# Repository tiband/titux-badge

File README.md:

# TiTux badge

## board

The board is designed in KiCad and uses a dual sided pcb while only using one side for the components. It features an ATtiny84 with 6 LEDs and a switch powered by a 3 V button cell. The example above was manufactured by [OSH Park].

## code

The challenge is to come up with your own interesting light shows, games, etc. for the badge. This repo includes a basic Arduino sketch using the [ATTinyCore] to get you started.

Use some crocodile clips and an AVR ISP programmer like a standard Arduino UNO with the [ISP sketch] and a 10 μF capacitor.

## licence

The design and example firmware are licenced under `GPL-3.0-or-later`.

[OSH Park]: https://oshpark.com/
[ATTinyCore]: https://github.com/SpenceKonde/ATTinyCore
[ISP sketch]: https://www.arduino.cc/en/tutorial/arduinoISP

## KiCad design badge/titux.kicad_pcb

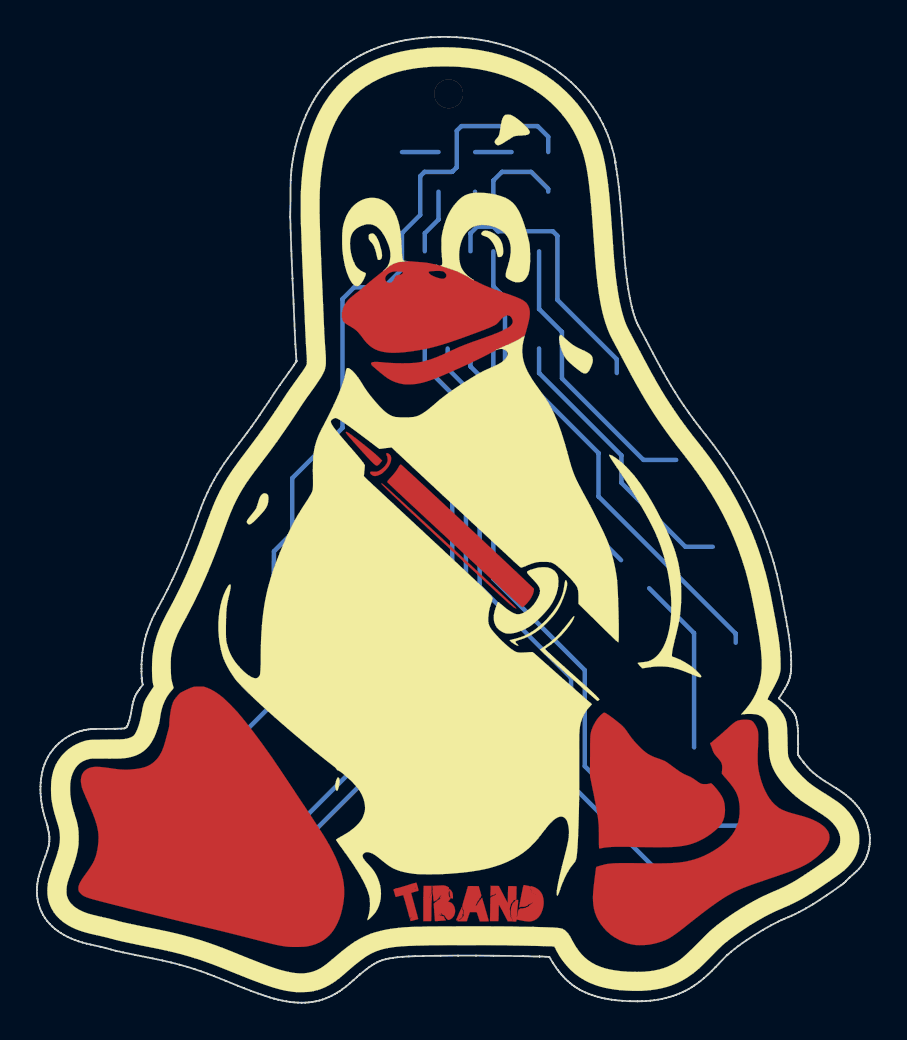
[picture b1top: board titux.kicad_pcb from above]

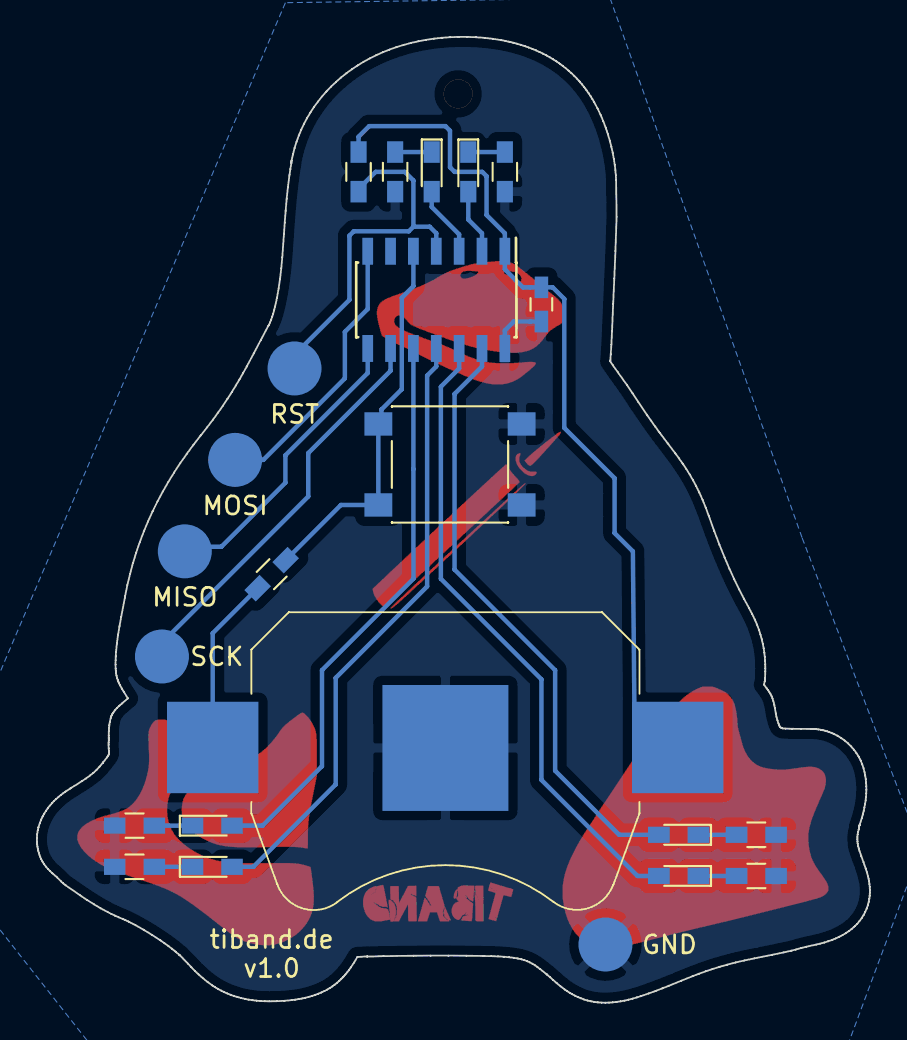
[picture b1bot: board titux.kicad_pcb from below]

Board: 2 copper layers, 46.3 x 53.7 mm, 23 parts (23 on the bottom side), 19 nets.

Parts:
BT1: Battery_Cell; KZH_20SMD_1x20mm-CoinCell
C1: 100n; C_0603_HandSoldering
D1, D2, D3, D4, D5, D6: LED_Small; LED_0603_HandSoldering
GND: Conn_01x01; KrokoPad
MISO: Conn_01x01; KrokoPad
MOSI: Conn_01x01; KrokoPad
R1, R2, R3, R4, R5, R6: R_Small; R_0603_HandSoldering
R10, R11: 10k; R_0603_HandSoldering
RST: Conn_01x01; KrokoPad
SCK: Conn_01x01; KrokoPad
SW1: SW_Push; Switch_SMD_rotated_6x6x4,3
U1: ATtiny84A-SSU; SOIC-14_3.9x8.7mm_Pitch1.27mm

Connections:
/LED_B1: D1.2, U1.12
/LED_B2: D3.2, U1.10
/LED_B3: D5.2, U1.3
/LED_R1: D2.2, U1.13
/LED_R2: D4.2, U1.11
/LED_R3: D6.2, U1.2
/MISO: MISO.1, U1.8
/MOSI: MOSI.1, U1.7
/RESET: R11.2, RST.1, U1.4
/SCK: SCK.1, U1.9
GND: BT1.2, C1.2, GND.1, R1.2, R2.2, R3.2, R4.2, R5.2, R6.2, SW1.1, U1.14
unnamed: D1.1, R1.1
unnamed: D2.1, R2.1
unnamed: D3.1, R3.1
unnamed: D4.1, R4.1
unnamed: D5.1, R5.1
unnamed: D6.1, R6.1
unnamed: R10.2, SW1.2, U1.5
VCC: BT1.1, C1.1, R10.1, R11.1, U1.1

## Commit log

2019-11-24 Initial version of the TI-Tux
2019-12-06 Refine titux
2020-01-05 Add simple example firmware for pulsating the leds
2020-01-05 Import version 1.0 of the board layout
2020-01-05 Add README and image
2020-01-06 Add GPLv3 licence file
